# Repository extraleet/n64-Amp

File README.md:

custom edit/rebuild from Bortis n64 Amp https://github.com/borti4938 thx Borti 

features:

-composite sync on Video -> Multi AV (Pin 9) -> compatible with every RGB Cable

-THS7374 Amplifier 4 channels

-LowPass Filter (enabled by closing the jumper)

-composite sync filtered by 330uF

Makes it easier to use RGB cables with n64 (pal/ntsc) rgb mods or ntsc consoles with vdc-nus chip.

(Consoles with denc,mav or avdc nus need also a rgb mod.)

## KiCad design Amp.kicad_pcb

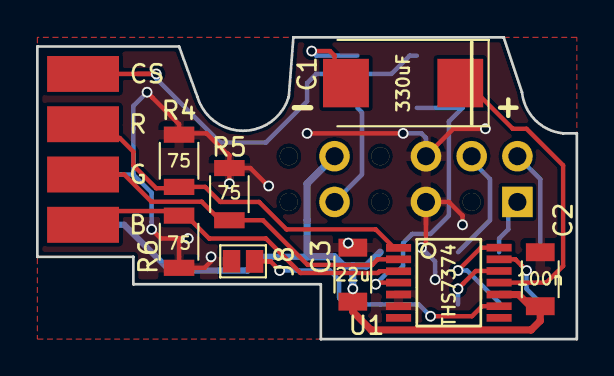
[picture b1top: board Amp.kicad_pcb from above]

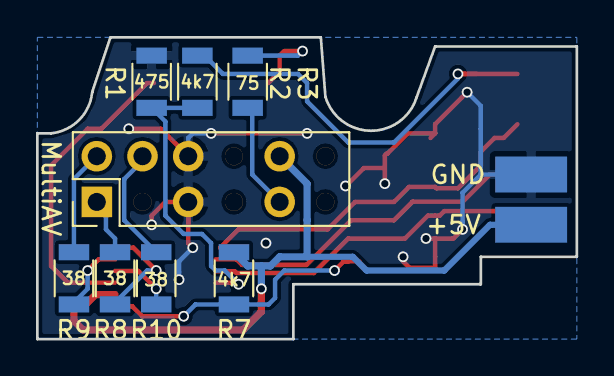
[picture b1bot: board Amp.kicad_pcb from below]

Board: 2 copper layers, 30.0 x 16.8 mm, 22 parts (10 on the bottom side), 17 nets.

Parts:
C1: 330uF; CP_Tantalum_Case-D_EIA-7343-31_Reflow
C2: 100n; C_1206
C3: 22u; C_1206
J1: MultiAV; Pin_Header_Straight_2x06_Pitch2.54mm
J2: CS; SMD_PAD_2x4
J3: R; SMD_PAD_2x4
J4: G; SMD_PAD_2x4
J5: B; SMD_PAD_2x4
J6: GND; SMD_PAD_2x4
J7: +5V; SMD_PAD_2x4
J8: GS2
R1: 475; R_1206
R2, R7: 4k7; R_1206
R3, R4, R5, R6: 75; R_1206
R8, R9, R10: 38; R_1206
U1: THS7374; SSOP-14

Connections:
+5V: C2.1, C3.1, J1.10, J7.1, R7.1, U1.10
B_OUT: J1.4, R10.1
CVIDEO_EXT: J1.9, R3.1
CVIDEO_OUT: C1.1, U1.11
GND: C2.2, C3.2, J1.5, J1.6, J6.1, J8.2, R1.1, R4.2, R5.2, R6.2, U1.5, U1.6
G_OUT: J1.2, R9.1
unnamed: C1.2, R3.2
unnamed: J2.1, R2.2
unnamed: J3.1, R4.1, U1.1
unnamed: J4.1, R5.1, U1.2
unnamed: J5.1, R6.1, U1.3
unnamed: J8.1, R7.2, U1.9
unnamed: R1.2, R2.1, U1.4
unnamed: R8.2, U1.14
unnamed: R9.2, U1.13
unnamed: R10.2, U1.12
R_OUT: J1.1, R8.1

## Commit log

2017-12-02 -first release
2017-12-02 -gerber
2017-12-02 -schematic as pdf
2017-12-02 -readme
2018-05-22 fixed some bugs
2018-05-22 Gerbers Added
